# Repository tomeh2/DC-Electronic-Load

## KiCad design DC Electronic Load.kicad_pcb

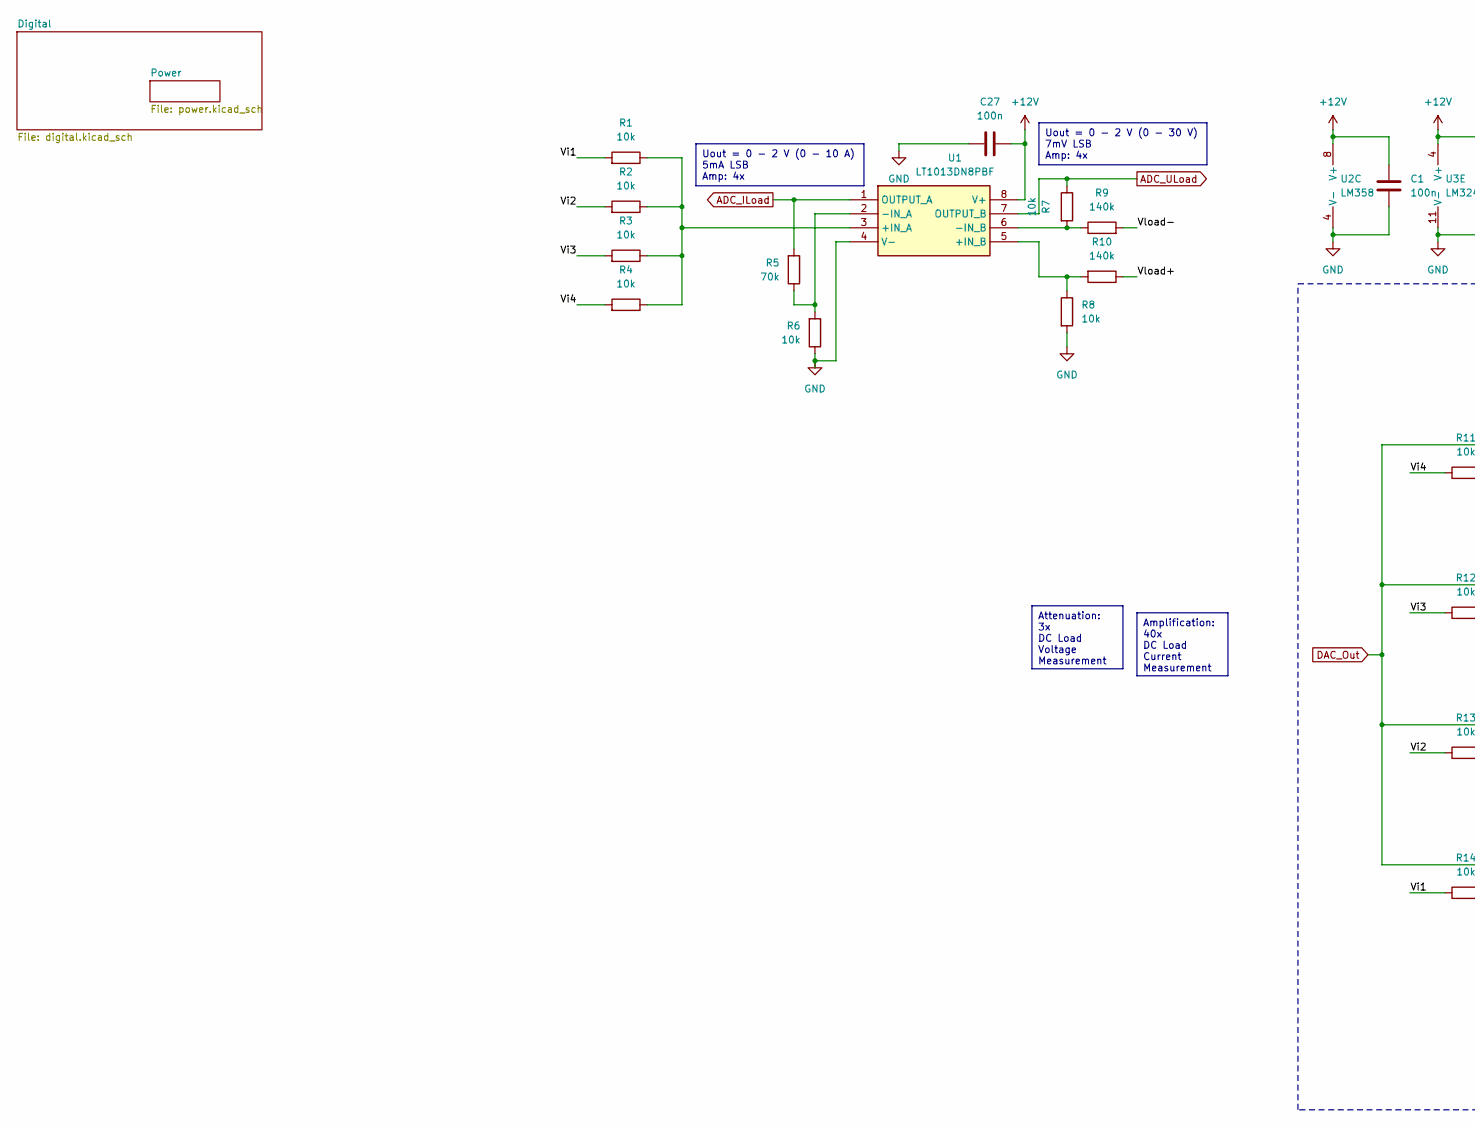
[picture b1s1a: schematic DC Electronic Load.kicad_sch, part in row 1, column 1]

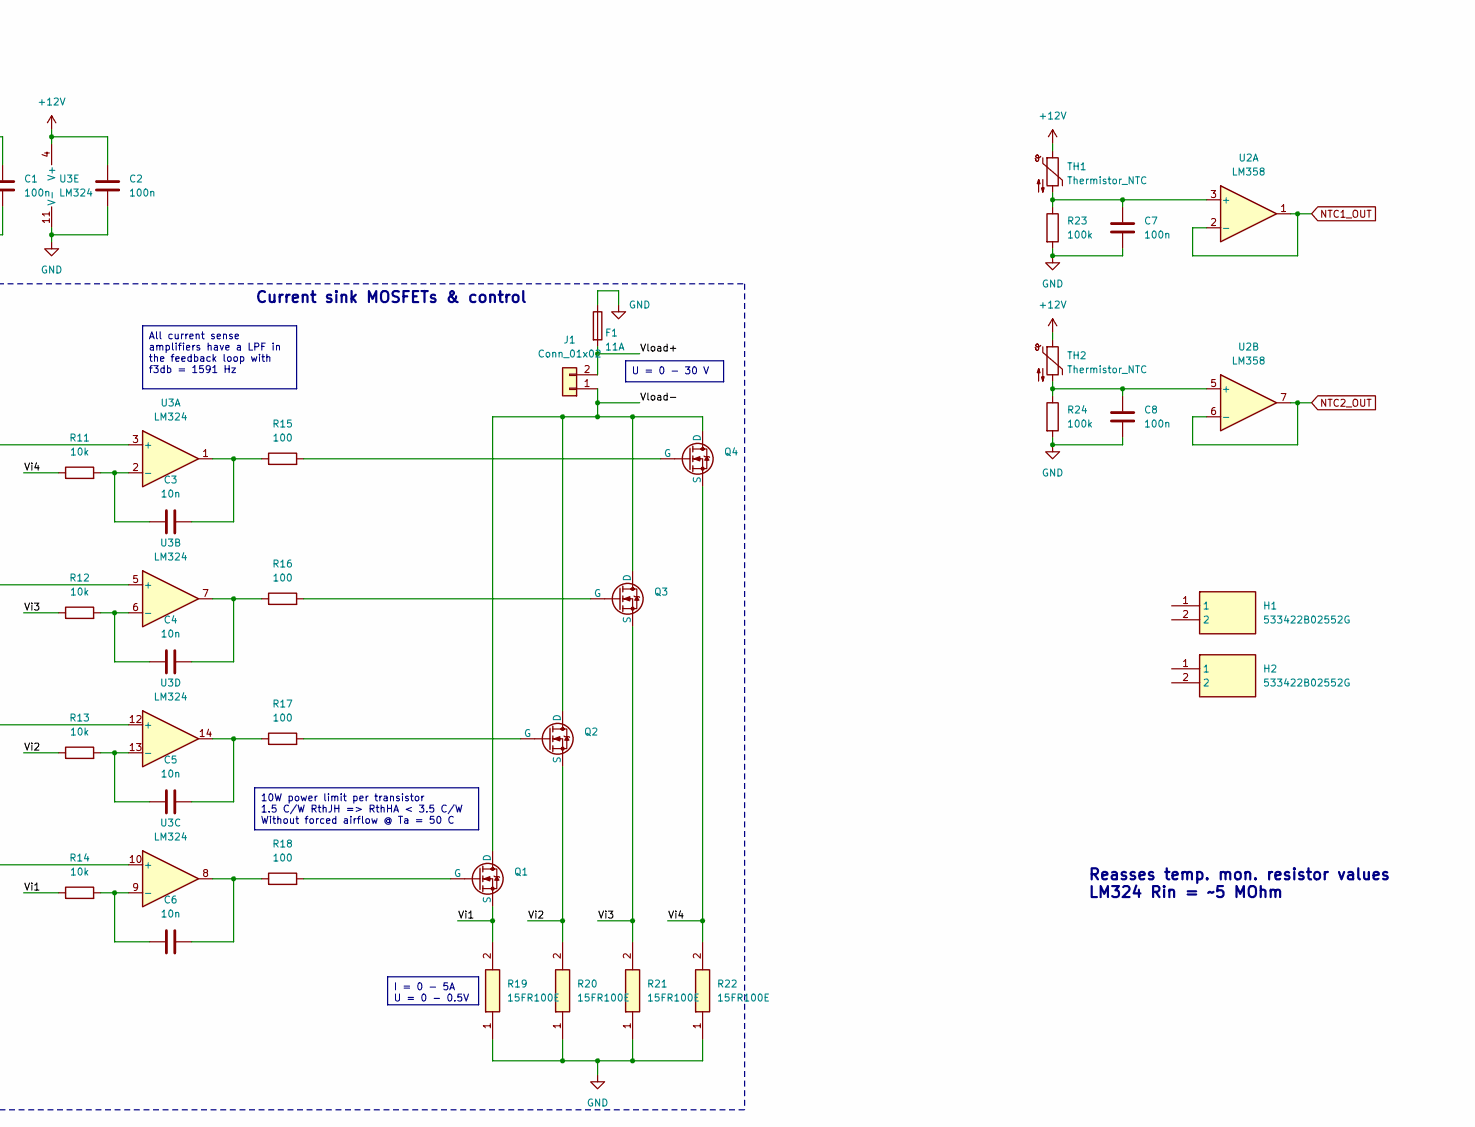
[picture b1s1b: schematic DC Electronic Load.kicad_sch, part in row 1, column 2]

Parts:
C1, C2, C27: 100n; C_Rect_L7.0mm_W2.5mm_P5.00mm; Mouser Part Number 594-K104K15X7RF53H5
C3, C4, C5, C6: 10n; C_Rect_L7.0mm_W2.5mm_P5.00mm; Mouser Part Number 594-K103K10X7RF53H5
C7, C8: 100n; C_Rect_L7.0mm_W2.5mm_P5.00mm
F1: 11A; Fuseholder_Clip-5x20mm_Littelfuse_100_Inline_P20.50x4.60mm_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; Mouser Part Number 576-65600001009
H1, H2: 533422B02552G; Mouser Part Number 532-533422B02552
J1: Conn_01x02; TerminalBlock_Phoenix_MKDS-1,5-2_1x02_P5.00mm_Horizontal; Mouser Part Number 490-TB005-762-02BE
Q1, Q2, Q3, Q4: IXTP100N04T2; TO-220-3_Vertical; Mouser Part Number 747-IXTP100N04T2
R1, R2, R3, R4, R6, R7, R8, R11, R12, R13, R14: 10k; R_Axial_DIN0204_L3.6mm_D1.6mm_P7.62mm_Horizontal; Mouser Part Number 594-5063JD10K1%TR
R5: 70k; R_Axial_DIN0204_L3.6mm_D1.6mm_P7.62mm_Horizontal; Mouser Part Number 603-MFR-25FTE52-30K
R9, R10: 140k; R_Axial_DIN0204_L3.6mm_D1.6mm_P7.62mm_Horizontal; Mouser Part Number 603-MFR-25FTE52-140K
R15, R16, R17, R18: 100; R_Axial_DIN0204_L3.6mm_D1.6mm_P7.62mm_Horizontal; Mouser Part Number 594-SFR2500001000JA5
R19, R20, R21, R22: 15FR100E; RESAD5740W107L2380D840; Mouser Part Number 588-15FR100E
R23, R24: 100k; R_Axial_DIN0204_L3.6mm_D1.6mm_P7.62mm_Horizontal
TH1, TH2: Thermistor_NTC; PinHeader_1x02_P2.54mm_Vertical
U1: LT1013DN8PBF; DIP-8_W7.62mm; Mouser Part Number 595-LT1013DIP
U2: LM358; DIP-8_W7.62mm
U3: LM324; DIP-14_W7.62mm; Mouser Part Number 595-LM324AN

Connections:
+12V: C1.1, C2.1, C27.2, TH1.1, TH2.1, U1.8 (V+), U2.8 (V+), U3.4 (V+); also elsewhere on the board
/Vi1: Q1.3 (S), R1.2, R14.1, R19.2
/Vi2: Q2.3 (S), R2.2, R13.1, R20.2
/Vi3: Q3.3 (S), R3.2, R12.1, R21.2
/Vi4: Q4.3 (S), R4.2, R11.1, R22.2
/Vload+: F1.2, J1.2, R10.1
/Vload-: J1.1, Q1.1 (D), Q2.1 (D), Q3.1 (D), Q4.1 (D), R9.2
ADC_ILoad: R5.2, U1.1 (OUTPUT_A); also elsewhere on the board
ADC_ULoad: R7.1, U1.7 (OUTPUT_B); also elsewhere on the board
DAC_Out: U3.3 (+), U3.5 (+), U3.10 (+), U3.12 (+); also elsewhere on the board
GND: C1.2, C2.2, C7.2, C8.2, C27.1, F1.1, R6.1, R8.2, R19.1, R20.1, R21.1, R22.1, R23.2, R24.2, U1.4 (V-), U2.4 (V-), U3.11 (V-); also elsewhere on the board
NTC1_OUT: U2.1, U2.2 (-); also elsewhere on the board
NTC2_OUT: U2.6 (-), U2.7; also elsewhere on the board
unnamed: C3.2, R15.1, U3.1
unnamed: C4.2, R16.1, U3.7
unnamed: C5.2, R17.1, U3.14
unnamed: C6.2, R18.1, U3.8
unnamed: Q1.2 (G), R18.2
unnamed: Q2.2 (G), R17.2
unnamed: Q3.2 (G), R16.2
unnamed: Q4.2 (G), R15.2
unnamed: R1.1, R2.1, R3.1, R4.1, U1.3 (+IN_A)
unnamed: R8.1, R10.2, U1.5 (+IN_B)
unnamed: R5.1, R6.2, U1.2 (-IN_A)
unnamed: R7.2, R9.1, U1.6 (-IN_B)
unnamed: C7.1, R23.1, TH1.2, U2.3 (+)
unnamed: C8.1, R24.1, TH2.2, U2.5 (+)
unnamed: C3.1, R11.2, U3.2 (-)
unnamed: C4.1, R12.2, U3.6 (-)
unnamed: C6.1, R14.2, U3.9 (-)
unnamed: C5.1, R13.2, U3.13 (-)

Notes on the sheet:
All current sense amplifiers have a LPF in the feedback loop with f3db = 1591 Hz
Uout = 0 - 2 V (0 - 10 A) 5mA LSB Amp: 4x
U = 0 - 30 V
10W power limit per transistor 1.5 C/W RthJH => RthHA < 3.5 C/W Without forced airflow @ Ta = 50 C
Amplification: 40x DC Load Current Measurement
Uout = 0 - 2 V (0 - 30 V) 7mV LSB Amp: 4x
I = 0 - 5A U = 0 - 0.5V
Attenuation: 3x DC Load Voltage Measurement
Current sink MOSFETs & control
Reasses temp. mon. resistor values LM324 Rin = ~5 MOhm

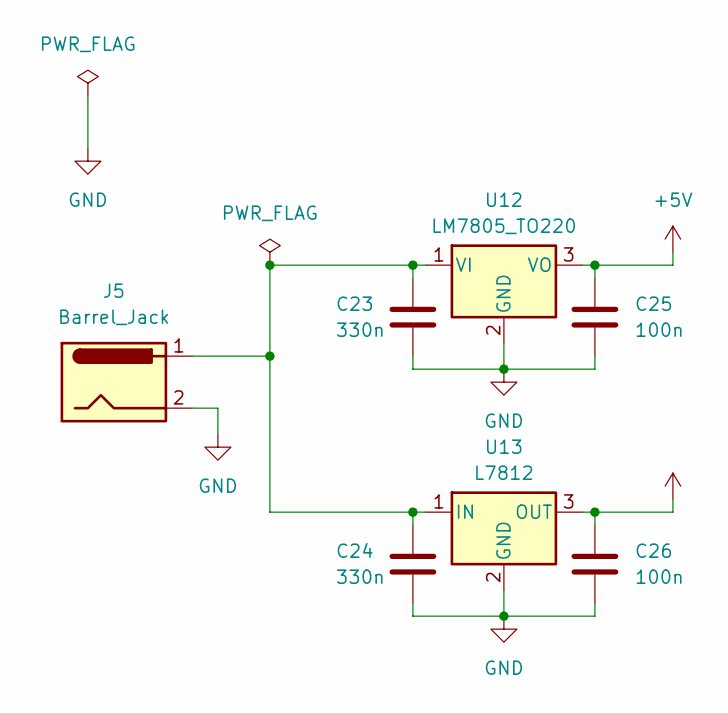
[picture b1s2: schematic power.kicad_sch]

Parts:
C23, C24: 330n; C_Rect_L7.0mm_W2.5mm_P5.00mm
C25, C26: 100n; C_Rect_L7.0mm_W2.5mm_P5.00mm
J5: Barrel_Jack; TerminalBlock_Phoenix_MKDS-1,5-2_1x02_P5.00mm_Horizontal
U12: LM7805_TO220; TO-220-3_Vertical
U13: L7812; TO-220-3_Vertical

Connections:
+5V: C25.1, U12.3 (VO); also elsewhere on the board
+12V: C26.1, U13.3 (OUT); also elsewhere on the board
GND: C23.2, C24.2, C25.2, C26.2, J5.2, U12.2 (GND), U13.2 (GND); also elsewhere on the board
unnamed: C23.1, C24.1, J5.1, U12.1 (VI), U13.1 (IN)

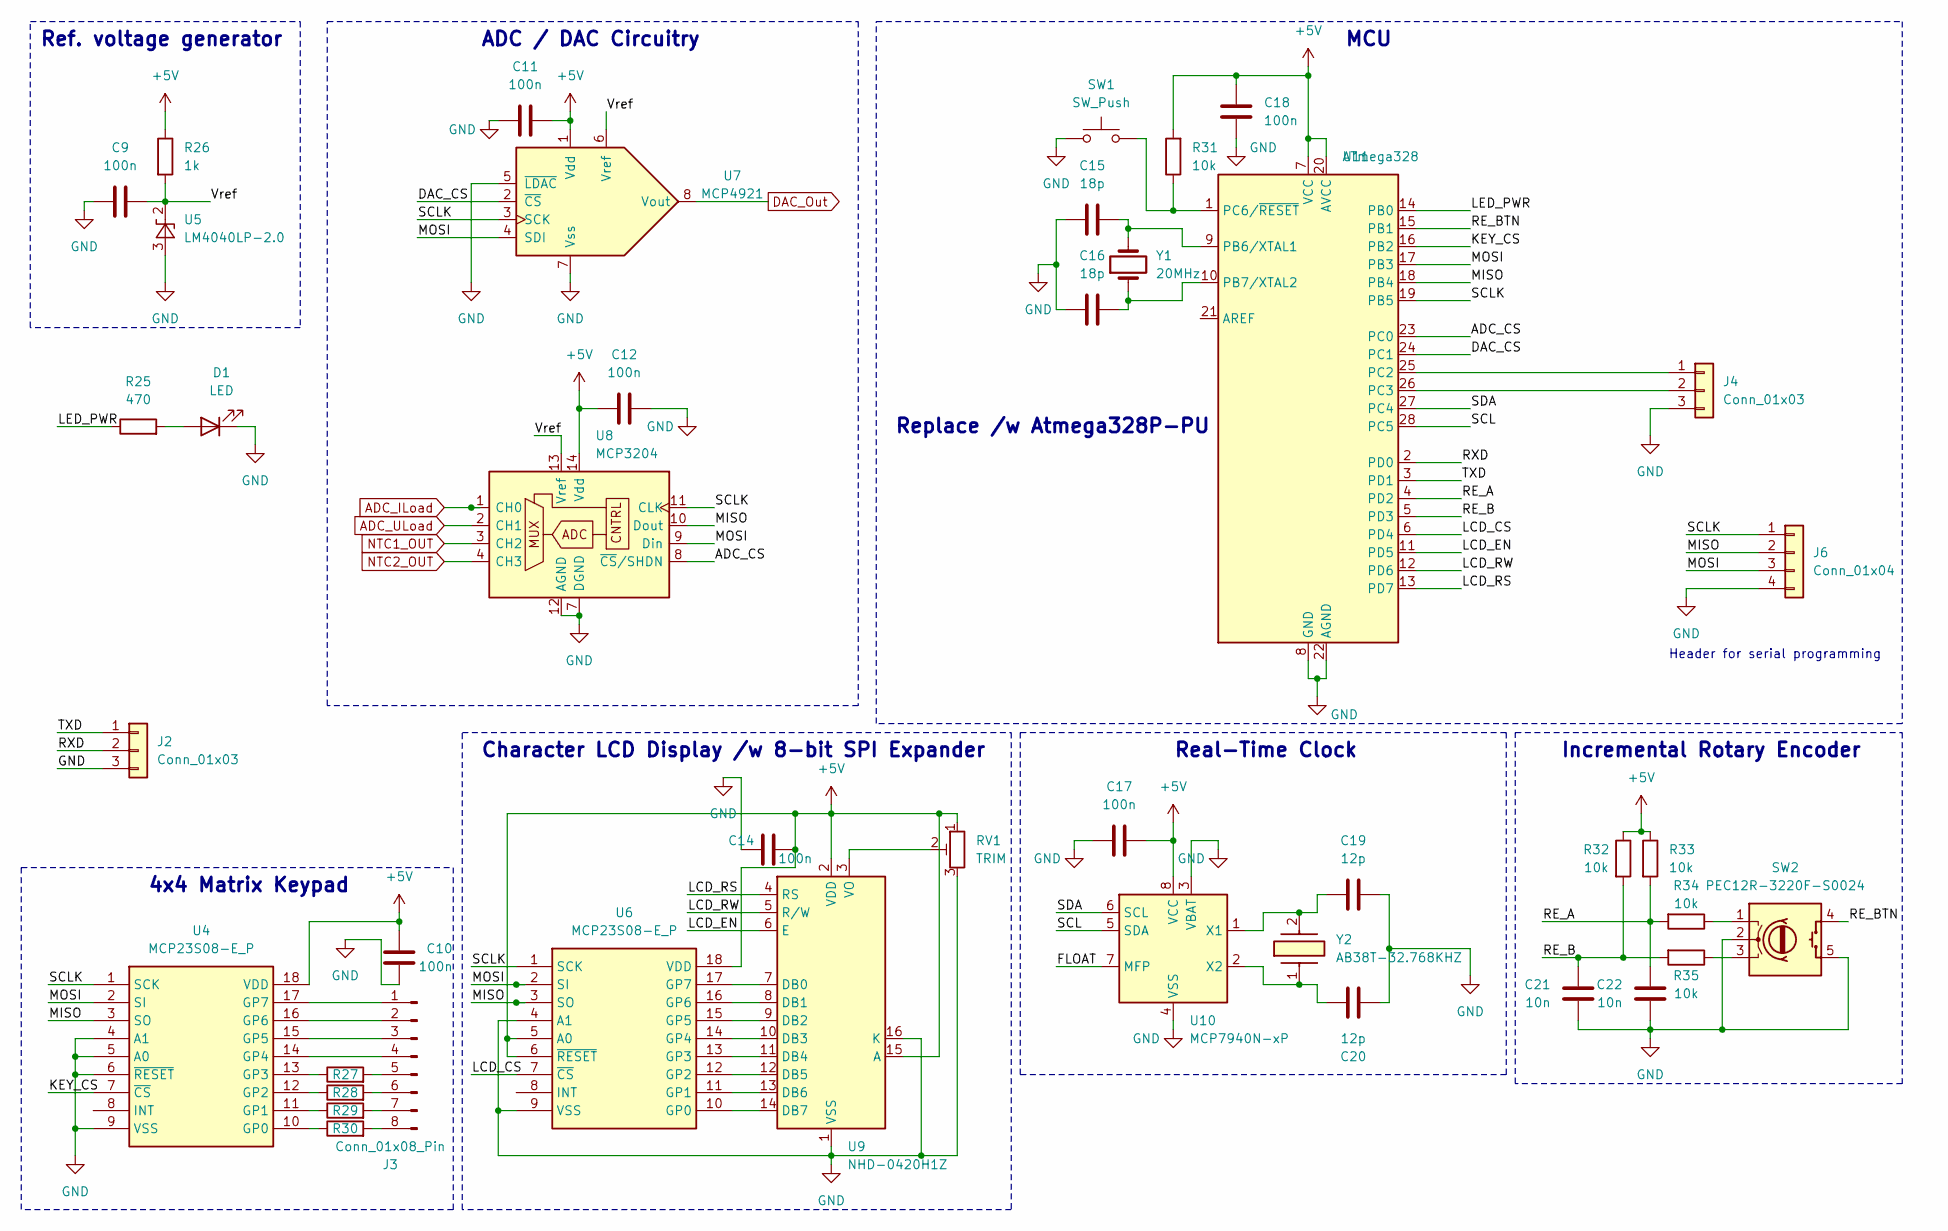
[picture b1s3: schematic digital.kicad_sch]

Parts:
C9, C10, C11, C12, C14, C17, C18: 100n; C_Rect_L7.0mm_W2.5mm_P5.00mm; Mouser Part Number 594-K104K15X7RF53H5
C15, C16: 18p; C_Disc_D5.0mm_W2.5mm_P5.00mm; Mouser Part Number 80-C317C180J2G
C19, C20: 12p; C_Disc_D5.0mm_W2.5mm_P5.00mm; Mouser Part Number 80-C317C120J5G
C21, C22: 10n; C_Rect_L7.0mm_W2.5mm_P5.00mm; Mouser Part Number 594-K104K15X7RF53H5
D1: LED; LED_D3.0mm; Mouser Part Number 696-SSL-LX30FT4GD
J2, J4: Conn_01x03; PinHeader_1x03_P2.54mm_Vertical; Mouser Part Number 649-78511-403HLF
J3: Conn_01x08_Pin; PinHeader_1x08_P2.54mm_Vertical
J6: Conn_01x04; PinHeader_1x04_P2.54mm_Vertical
R25: 470; R_Axial_DIN0204_L3.6mm_D1.6mm_P7.62mm_Horizontal; Mouser Part Number 603-MFR-25FTE52-470R
R26, R27, R28, R29, R30: 1k; R_Axial_DIN0204_L3.6mm_D1.6mm_P7.62mm_Horizontal; Mouser Part Number 603-MFR-25FTE52-1K
R31, R32, R33, R34, R35: 10k; R_Axial_DIN0204_L3.6mm_D1.6mm_P7.62mm_Horizontal; Mouser Part Number 594-5063JD10K1%TR
RV1: TRIM; Potentiometer_ACP_CA9-H2,5_Horizontal; Mouser Part Number 531-PT10V-20K
SW1: SW_Push; SW_PUSH_6mm; Mouser Part Number 179-TS026650BK160LCR
SW2: PEC12R-3220F-S0024; PinHeader_1x05_P2.54mm_Vertical; Mouser Part Number 652-PEC12R3220FS0024
U4, U6: MCP23S08-E_P; DIP-18_W7.62mm; Mouser Part Number 579-MCP23S08-E/P
U5: LM4040LP-2.0; TO-92_Inline; Mouser Part Number 595-LM4040C20ILPR
U7: MCP4921; DIP-8_W7.62mm; Mouser Part Number 579-MCP4921-E/P
U8: MCP3204; DIP-14_W7.62mm
U9: NHD-0420H1Z; PinHeader_1x16_P2.54mm_Vertical; Mouser Part Number 763-NHD0420H1ZFSWGBW
U10: MCP7940N-xP; DIP-8_W7.62mm; Mouser Part Number 579-MCP7940N-I/P
U11: ATmega328; DIP-28_W7.62mm; Mouser Part Number 556-ATMEGA8A-PU
Y1: 20MHz; Crystal_HC49-U_Vertical; Mouser Part Number 815-ABL16000MHZB4YT
Y2: AB38T-32.768KHZ; AB38T32768KHZ; Mouser Part Number 815-AB38T-32.768KHZ

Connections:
+5V: C10.2, C11.1, C12.2, C14.1, C17.1, C18.2, R26.1, R31.2, R32.1, R33.1, RV1.1, U4.18 (VDD), U6.5 (A0), U6.6 (~RESET), U6.18 (VDD), U7.1 (Vdd), U8.14 (Vdd), U9.2 (VDD), U9.15 (A), U10.8 (VCC), U11.7 (VCC), U11.20 (AVCC); also elsewhere on the board
/Digital/ADC_CS: U8.8 (~CS/SHDN), U11.23 (PC0)
/Digital/DAC_CS: U7.2 (~CS), U11.24 (PC1)
/Digital/FLOAT: U10.7 (MFP)
/Digital/KEY_CS: U4.7 (~CS), U11.16 (PB2)
/Digital/LCD_CS: U6.7 (~CS), U11.6 (PD4)
/Digital/LCD_EN: U9.6 (E), U11.11 (PD5)
/Digital/LCD_RS: U9.4 (RS), U11.13 (PD7)
/Digital/LCD_RW: U9.5 (R/W), U11.12 (PD6)
/Digital/LED_PWR: R25.1, U11.14 (PB0)
/Digital/MISO: J6.2, U4.3 (SO), U6.3 (SO), U8.10 (Dout), U11.18 (PB4)
/Digital/MOSI: J6.3, U4.2 (SI), U6.2 (SI), U7.4 (SDI), U8.9 (Din), U11.17 (PB3)
/Digital/RE_A: C22.2, R33.2, R34.2, U11.4 (PD2)
/Digital/RE_B: C21.2, R32.2, R35.2, U11.5 (PD3)
/Digital/RE_BTN: SW2.4 (S1), U11.15 (PB1)
/Digital/RXD: J2.2, U11.2 (PD0)
/Digital/SCL: U10.5 (SDA), U11.28 (PC5)
/Digital/SCLK: J6.1, U4.1 (SCK), U6.1 (SCK), U7.3 (SCK), U8.11 (CLK), U11.19 (PB5)
/Digital/SDA: U10.6 (SCL), U11.27 (PC4)
/Digital/TXD: J2.1, U11.3 (PD1)
/Digital/Vref: C9.2, R26.2, U5.2 (K), U7.6 (Vref), U8.13 (Vref)
ADC_ILoad: U8.1 (CH0); also elsewhere on the board
ADC_ULoad: U8.2 (CH1); also elsewhere on the board
DAC_Out: U7.8 (Vout); also elsewhere on the board
GND: C9.1, C10.1, C11.2, C12.1, C14.2, C15.1, C16.1, C17.2, C18.1, C19.2, C20.2, C21.1, C22.1, D1.1 (K), J2.3, J4.3, J6.4, RV1.3, SW1.1, SW2.2 (C), SW2.5 (S2), U4.4 (A1), U4.5 (A0), U4.6 (~RESET), U4.9 (VSS), U5.3 (A), U6.4 (A1), U6.9 (VSS), U7.5 (~LDAC), U7.7 (Vss), U8.7 (DGND), U8.12 (AGND), U9.1 (VSS), U9.16 (K), U10.3 (VBAT), U10.4 (VSS), U11.8 (GND), U11.22 (AGND); also elsewhere on the board
NTC1_OUT: U8.3 (CH2); also elsewhere on the board
NTC2_OUT: U8.4 (CH3); also elsewhere on the board
unnamed: D1.2 (A), R25.2
unnamed: J3.1, U4.17 (GP7)
unnamed: J3.2, U4.16 (GP6)
unnamed: J3.3, U4.15 (GP5)
unnamed: J3.4, U4.14 (GP4)
unnamed: J3.5, R27.2
unnamed: J3.6, R28.2
unnamed: J3.7, R29.2
unnamed: J3.8, R30.2
unnamed: J4.1, U11.25 (PC2)
unnamed: J4.2, U11.26 (PC3)
unnamed: R34.1, SW2.1 (A)
unnamed: R35.1, SW2.3 (B)
unnamed: R30.1, U4.10 (GP0)
unnamed: R29.1, U4.11 (GP1)
unnamed: R28.1, U4.12 (GP2)
unnamed: R27.1, U4.13 (GP3)
unnamed: U6.10 (GP0), U9.14 (DB7)
unnamed: U6.11 (GP1), U9.13 (DB6)
unnamed: U6.12 (GP2), U9.12 (DB5)
unnamed: U6.13 (GP3), U9.11 (DB4)
unnamed: U6.14 (GP4), U9.10 (DB3)
unnamed: U6.15 (GP5), U9.9 (DB2)
unnamed: U6.16 (GP6), U9.8 (DB1)
unnamed: U6.17 (GP7), U9.7 (DB0)
unnamed: RV1.2, U9.3 (VO)
unnamed: C19.1, U10.1 (X1), Y2.2
unnamed: C20.1, U10.2 (X2), Y2.1
unnamed: C15.2, U11.9 (PB6/XTAL1), Y1.2
unnamed: C16.2, U11.10 (PB7/XTAL2), Y1.1
unnamed: R31.1, SW1.2, U11.1 (PC6/~RESET)

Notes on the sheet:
Incremental Rotary Encoder
MCU
ADC / DAC Circuitry
Character LCD Display /w 8-bit SPI Expander
Replace /w Atmega328P-PU
Real-Time Clock
Header for serial programming
Ref. voltage generator
4x4 Matrix Keypad

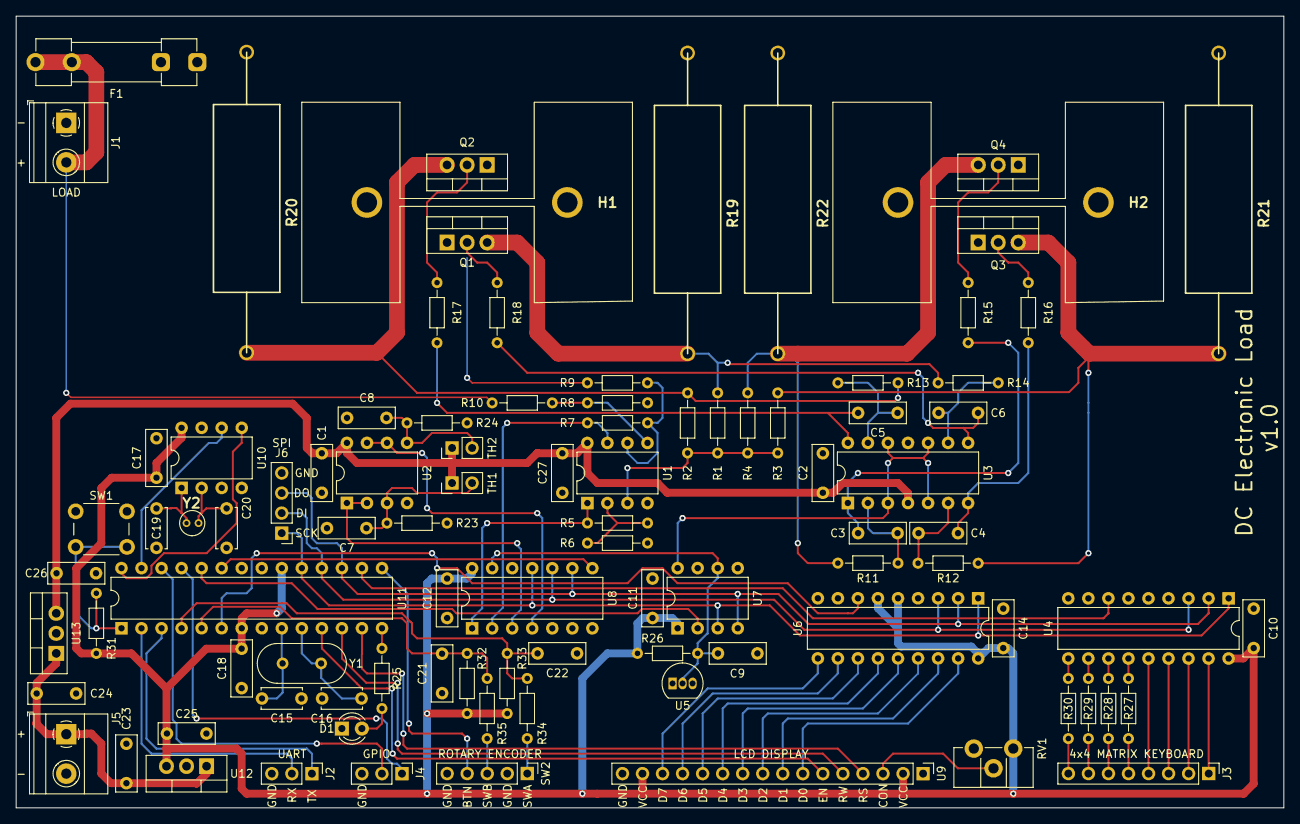
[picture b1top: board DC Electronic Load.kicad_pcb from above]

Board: 2 copper layers, 160.7 x 100.3 mm, 95 parts (0 on the bottom side), 83 nets.

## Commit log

2024-09-01 First commit of a finished project
